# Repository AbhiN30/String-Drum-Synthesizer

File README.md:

# String/Drum Synthesizer (Initial Project Proposal)

## Team Members:
- Abhi Nayak (arnayak2) 
- Joel Schurgin (joelbs3)

## Problem
A musical artist brings with them a sense of how to evoke certain emotions or create particular atmospheres, but may lack the technical knowledge to bring it to life. Sound design can be challenging as it involves crafting the unique timbres and textures that define a piece of music, which can be both an art and a science. The learning curve is steep, not only because it requires a grasp of complex technical tools but also because it demands a creative intuition that isn't easily taught. Musicians and producers must learn to navigate a vast array of software and hardware tools, each with its own set of knobs, sliders, and buttons. Understanding how to shape sounds means diving deep into the physics of sound waves, the principles of digital signal processing, and the subtleties of different synthesis methods. This process can feel overwhelming, especially for beginners who might feel lost amidst the jargon and the sheer number of options.

## Solution
Our proposal is to build a synthesizer. A synthesizer is a machine that is capable of producing a range of sounds when given a simple key or noise pulse. The range of sounds are controlled by a set of parameters such as filter cutoffs, oscillator types, low frequency oscillators, etc. The proposed solution is two-fold. The first part of the project is to build emotive knobs that feature descriptive ranges such as soft to aggressive or thin to thick. These knobs would also control the internal parameters of the system to achieve the desired effects on the input sound. The other part is to create a system that records a sound and finds the best way to set the synthesizer's internal parameters to recreate it. The intended work flow of this device for a musical artist is to record a sound, tweak the knobs, and play that sound by pressing a key on a MIDI keyboard. It is up to the musician to record the sound into their own recording software for further manipulation.

# Solution Components
## Subsystem 1: Power Block

Purpose/Requirements: This subsystem must be able to power the processor and the USB keyboard. Capacitors will be used to stabilize the power block.

Components:

- 5V DC Power Supply Adapter
- Capacitors
- Subsystem 2: Synthesizer

## Subsystem 2: Software Synthesizer
Purpose/Requirements: This subsystem will generate sounds using the Karplus Strong algorithm which features a pulse generator and an echo chamber (modeled with digital delay, feedback, and filtering). When a note is played on a USB keyboard, this component must be able to change the pitch based on which key is pressed. The algorithm’s parameters must be controllable using potentiometers, but several parameters can be determined as a function of one knob. We chose the Karplus Strong algorithm to reduce the computational load, but we are modifying certain aspects to allow for a greater range of sounds. The pulse that we will use is a blend of noise and sine wave oscillator which are added together and distorted. In addition, there will be some soft distortion applied on the output. In addition, the echo chamber will use 3 IIR filters: highpass, lowpass, and a bell. The choice to use IIR filters is to lower the amount of computation.

We made a demo of the synthesizer algorithm using a digital audio workstation in order to play with parameters and determine the names of the emotive knobs. Below are the emotive knobs and how the corresponding synth parameters should change to implement them:

Aggression

- Synth Params: Pulse distortion, output distortion
- Knob Left: Low distortion
- Knob Right: High distortion

Brightness

- Synth Param: Low pass filter cutoff
- Knob Left: 20 Hz
- Knob Right: 20 kHz

Boominess

- Synth Param: High pass Cutoff
- Knob Left: 20 kHz
- Knob Center: Note pitch
- Knob Right: 20 Hz

Dampening

- Synth Param: Bell Q
- Knob Left: High Q
- Knob Right: Low Q

*Not sure what to call this yet, but it affects how the echo chamber resonates. Note: setting this to around 3.6 kHz sounds good, so it could be fine to keep this completely internal and forgo the corresponding knob.

- Synth Param: Bell frequency
- Knob Left: 20 hz
- Knob Right: 20 kHz

Scratchiness

- Synth Param: Length of pulse
- Knob Left: 0
- Knob Center: 1/(Note pitch)
- Knob Right: 4/(Note pitch)

Sharpness

- Synth Param: Mix between pulse noise and oscillator
- Knob Left: Pulse consists of only oscillator
- Knob Right: Pulse consists of only noise

*Strike weight => Corresponds to simulated weight of object striking the string/drum head.

- Synth Param: Pulse oscillator pitch
- Knob Left: 20 kHz
- Knob Right: 20 hz

Notes:
- The value "note pitch" is determined by USB keyboard input.
- Bell gain is fixed and should be set to attenuate the signal.

Components:

- Microprocessor
- DAC
- Potentiometers for parameters (linear, should be able to snap to center position if center value has meaning other should be smooth all the way through)
- USB Port

## Subsystem 3: Amplifier
Purpose/Requirements: This subsystem should output the smallest possible signal to noise ratio through a guitar cable or headphones. In order to achieve this we will experiment with using several inverting op-amp amplifier circuits in parallel and summing them together with an inverting mixer. The gain of each amplifier will be set, but the volume control will be part of the inverting mixer circuit.

Components:

- Mono 1/4in audio jack
- 4 Op-amps
- Logarithmic Potentiometer (for volume control)

## Subsystem 4: Screen/Monitor
Purpose/Requirements: This subsystem should display the waveform of the sound being processed. The purpose of this subsystem is for the user to be able to receive a visual representation of the sound they are developing using their input pulse and emotive knob manipulations. The screen could enhance the usability of the synthesizer by providing visual indicators or icons for each emotive knob, making it easier for users to identify how different settings affect the overall sound. This would bridge the gap between technical sound parameters and intuitive control.

Components:

- Mono 1/4in audio jack
- Op-amp/Transistors
- Raspberry Pi Screen, 7 inch portable monitor external display
# Criterion For Success
High-Level Goals:

1) Get a simple sound, such as a sine wave at 440 Hz, out of DAC output from the synthesizer subsystem. Should be viewable in an oscilloscope, but not important to hear yet.
2) Add potentiometers to the synthesizer and use to control pitch of simple sound for testing.
3) Build the amplifier in order to hear the previously described sound.
4) Add USB port and code for parsing keyboard input.
5) Use synthesizer algorithms to implement the emotive knobs, starting with the pulse generator and then building the echo chamber.
Reach Goal:

6) Implement the screen into the entire system. It will show the waveform of the generated sound, including its amplitude, frequency, and potential distortions. This helps users better grasp the effect of parameters like distortion, brightness, dampening, etc. This visualization would assist the user in creating more precise and desired sounds.

Important Notes:

-The screen is peripheral and not required for the rest of the system to operate. Therefore implementing it is a reach goal.

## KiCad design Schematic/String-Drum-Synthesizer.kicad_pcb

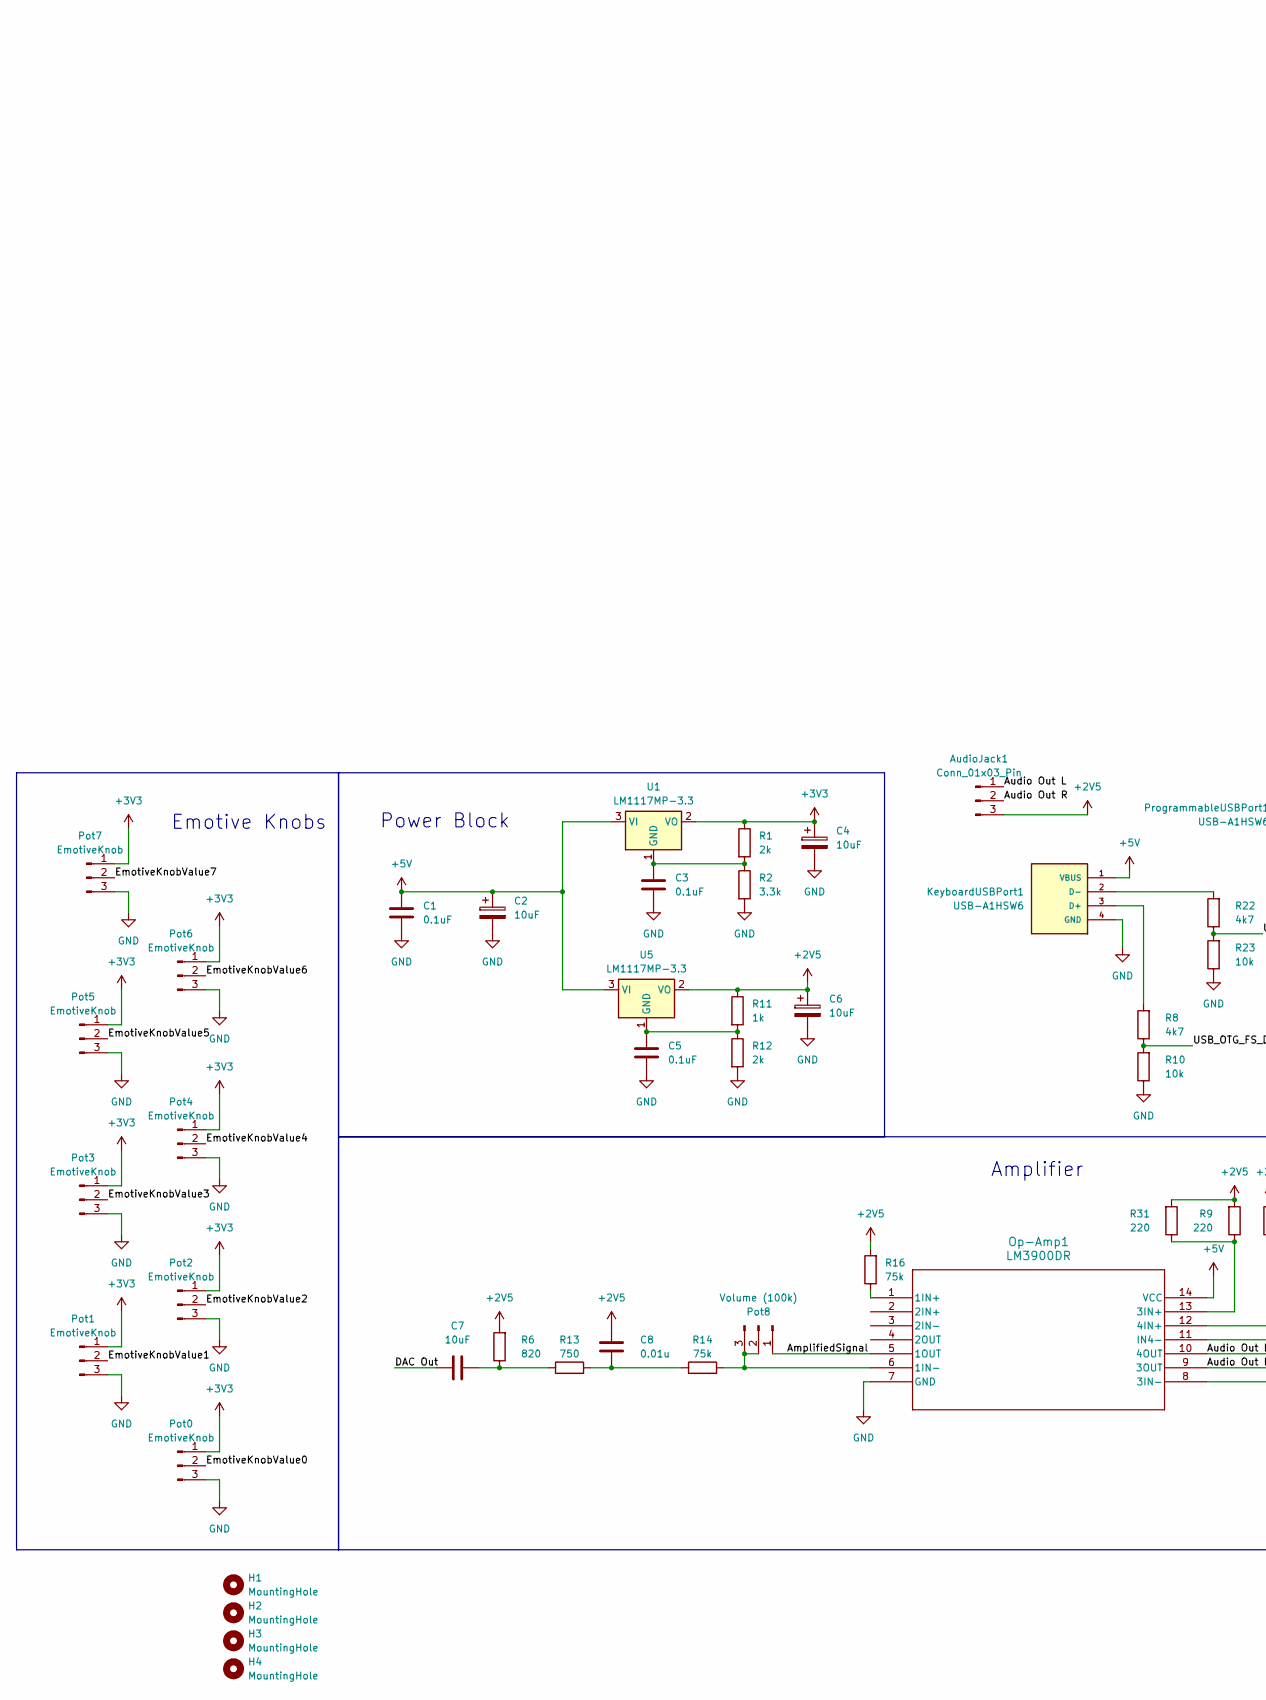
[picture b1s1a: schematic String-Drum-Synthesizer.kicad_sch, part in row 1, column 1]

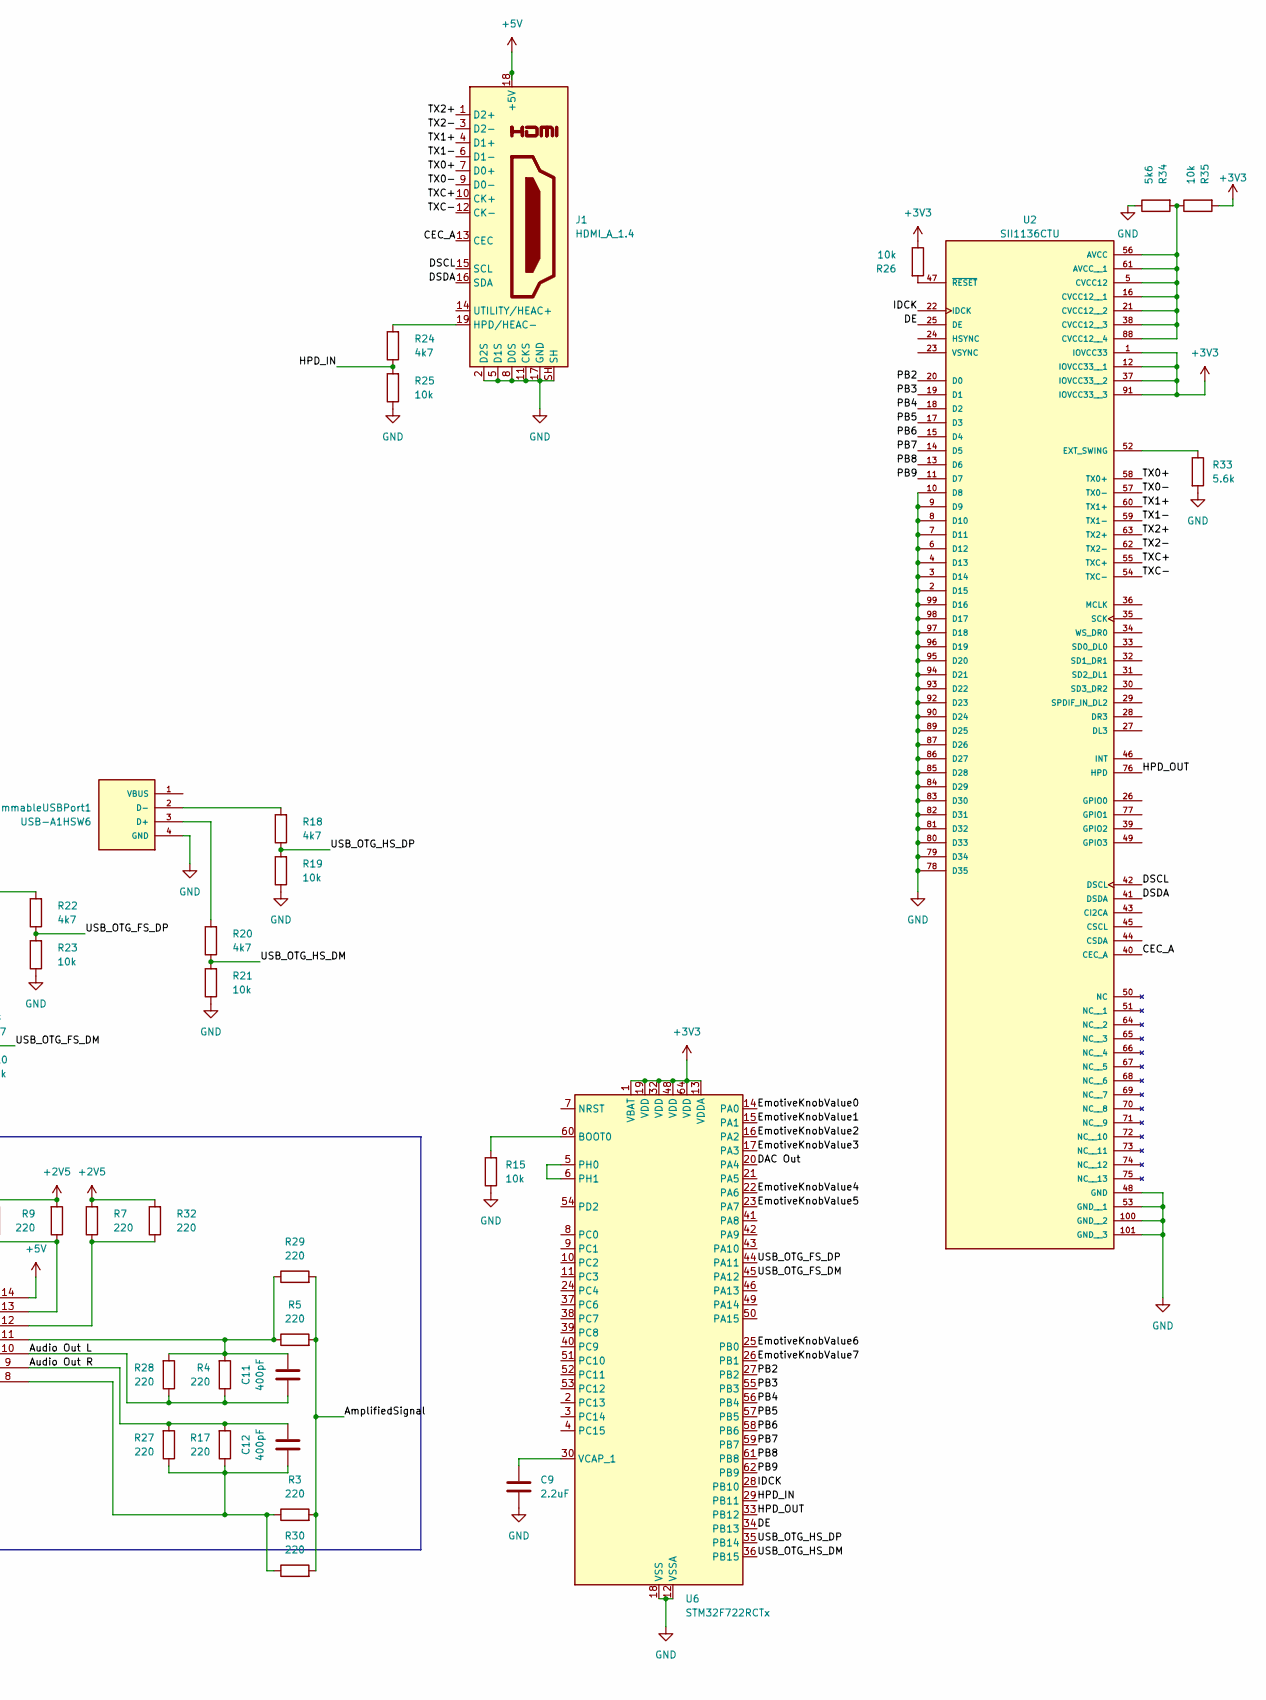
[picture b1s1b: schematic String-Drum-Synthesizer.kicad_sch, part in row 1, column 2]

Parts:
AudioJack1: Conn_01x03_Pin; Molex_KK-254_AE-6410-03A_1x03_P2.54mm_Vertical
C1, C3, C5: 0.1uF; C_Disc_D6.0mm_W4.4mm_P5.00mm
C2, C4, C6, C7: 10uF; CP_Radial_D7.5mm_P2.50mm
C8: 0.01u; C_Disc_D6.0mm_W4.4mm_P5.00mm
C9: 2.2uF; C_Disc_D6.0mm_W4.4mm_P5.00mm
C11, C12: 400pF; C_Disc_D6.0mm_W4.4mm_P5.00mm
H1, H2, H3, H4: MountingHole; MountingHole_3.2mm_M3
J1: HDMI_A_1.4; HDMI_A_Molex_208658-1001_Horizontal
KeyboardUSBPort1: USB-A1HSW6; OST_USB-A1HSW6; PARTREV A
Op-Amp1: LM3900DR; DIP-14_W7.62mm_Socket
Pot0, Pot1, Pot2, Pot3, Pot4, Pot5, Pot6, Pot7: EmotiveKnob; Molex_KK-254_AE-6410-03A_1x03_P2.54mm_Vertical
Pot8: Volume (100k); Molex_KK-254_AE-6410-03A_1x03_P2.54mm_Vertical
ProgrammableUSBPort1: USB-A1HSW6; OST_USB-A1HSW6; PARTREV A
R1, R12: 2k; R_Axial_DIN0207_L6.3mm_D2.5mm_P7.62mm_Horizontal
R2: 3.3k; R_Axial_DIN0207_L6.3mm_D2.5mm_P7.62mm_Horizontal
R3, R4, R5, R7, R9, R17, R27, R28, R29, R30, R31, R32: 220; R_Axial_DIN0207_L6.3mm_D2.5mm_P7.62mm_Horizontal
R6: 820; R_Axial_DIN0207_L6.3mm_D2.5mm_P7.62mm_Horizontal
R8, R18, R20, R22, R24: 4k7; R_Axial_DIN0207_L6.3mm_D2.5mm_P7.62mm_Horizontal
R10, R15, R19, R21, R23, R25, R26, R35: 10k; R_Axial_DIN0207_L6.3mm_D2.5mm_P7.62mm_Horizontal
R11: 1k; R_Axial_DIN0207_L6.3mm_D2.5mm_P7.62mm_Horizontal
R13: 750; R_Axial_DIN0207_L6.3mm_D2.5mm_P7.62mm_Horizontal
R14, R16: 75k; R_Axial_DIN0207_L6.3mm_D2.5mm_P7.62mm_Horizontal
R33: 5.6k; R_Axial_DIN0207_L6.3mm_D2.5mm_P7.62mm_Horizontal
R34: 5k6; R_Axial_DIN0207_L6.3mm_D2.5mm_P7.62mm_Horizontal
U1, U5: LM1117MP-3.3; SOT-223-3_TabPin2
U2: SII1136CTU; TQFP-100-1EP_14x14mm_P0.5mm_EP5x5mm
U6: STM32F722RCTx; LQFP-64_10x10mm_P0.5mm

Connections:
+2V5: AudioJack1.3, C6.1, C8.1, R6.2, R7.2, R9.2, R11.1, R16.2, R31.2, R32.2, U5.2 (VO)
+3V3: C4.1, Pot0.1, Pot1.1, Pot2.1, Pot3.1, Pot4.1, Pot5.1, Pot6.1, Pot7.1, R1.1, R26.1, R35.2, U1.2 (VO), U2.1 (IOVCC33), U2.12 (IOVCC33__1), U2.37 (IOVCC33__2), U2.91 (IOVCC33__3), U6.1 (VBAT), U6.13 (VDDA), U6.19 (VDD), U6.32 (VDD), U6.48 (VDD), U6.64 (VDD)
+5V: C1.1, C2.1, J1.18 (+5V), KeyboardUSBPort1.1 (VBUS), Op-Amp1.14 (VCC), U1.3 (VI), U5.3 (VI); also elsewhere on the board
/AmplifiedSignal: Op-Amp1.5 (1OUT), Pot8.1, R3.2, R5.2, R29.2, R30.2; also elsewhere on the board
/Audio Out L: AudioJack1.1, C11.1, Op-Amp1.10 (4OUT), R4.1, R28.1; also elsewhere on the board
/Audio Out R: AudioJack1.2, C12.2, Op-Amp1.9 (3OUT), R17.2, R27.2; also elsewhere on the board
/CEC_A: J1.13 (CEC), U2.40 (CEC_A)
/DAC Out: C7.1, U6.20 (PA4)
/DE: U2.25 (DE), U6.34 (PB13)
/DSCL: J1.15 (SCL), U2.42 (DSCL)
/DSDA: J1.16 (SDA), U2.41 (DSDA)
/EmotiveKnobValue0: Pot0.2, U6.14 (PA0)
/EmotiveKnobValue1: Pot1.2, U6.15 (PA1)
/EmotiveKnobValue2: Pot2.2, U6.16 (PA2)
/EmotiveKnobValue3: Pot3.2, U6.17 (PA3)
/EmotiveKnobValue4: Pot4.2, U6.22 (PA6)
/EmotiveKnobValue5: Pot5.2, U6.23 (PA7)
/EmotiveKnobValue6: Pot6.2, U6.25 (PB0)
/EmotiveKnobValue7: Pot7.2, U6.26 (PB1)
/HPD_IN: R24.1, R25.2, U6.29 (PB11)
/HPD_OUT: U2.76 (HPD), U6.33 (PB12)
/IDCK: U2.22 (IDCK), U6.28 (PB10)
/PB2: U2.20 (D0), U6.27 (PB2)
/PB3: U2.19 (D1), U6.55 (PB3)
/PB4: U2.18 (D2), U6.56 (PB4)
/PB5: U2.17 (D3), U6.57 (PB5)
/PB6: U2.15 (D4), U6.58 (PB6)
/PB7: U2.14 (D5), U6.59 (PB7)
/PB8: U2.13 (D6), U6.61 (PB8)
/PB9: U2.11 (D7), U6.62 (PB9)
/TX0+: J1.7 (D0+), U2.58 (TX0+)
/TX0-: J1.9 (D0-), U2.57 (TX0-)
/TX1+: J1.4 (D1+), U2.60 (TX1+)
/TX1-: J1.6 (D1-), U2.59 (TX1-)
/TX2+: J1.1 (D2+), U2.63 (TX2+)
/TX2-: J1.3 (D2-), U2.62 (TX2-)
/TXC+: J1.10 (CK+), U2.55 (TXC+)
/TXC-: J1.12 (CK-), U2.54 (TXC-)
/USB_OTG_FS_DM: R8.1, R10.2, U6.45 (PA12)
/USB_OTG_FS_DP: R22.1, R23.2, U6.44 (PA11)
/USB_OTG_HS_DM: R20.1, R21.2, U6.36 (PB15)
/USB_OTG_HS_DP: R18.1, R19.2, U6.35 (PB14)
GND: C1.2, C2.2, C3.2, C4.2, C5.2, C6.2, C9.2, J1.2 (D2S), J1.5 (D1S), J1.8 (D0S), J1.11 (CKS), J1.17 (GND), J1.SH, KeyboardUSBPort1.4 (GND), Op-Amp1.7 (GND), Pot0.3, Pot1.3, Pot2.3, Pot3.3, Pot4.3, Pot5.3, Pot6.3, Pot7.3, ProgrammableUSBPort1.4 (GND), R2.2, R10.1, R12.2, R15.1, R19.1, R21.1, R23.1, R25.1, R33.2, R34.1, U2.2 (D15), U2.3 (D14), U2.4 (D13), U2.6 (D12), U2.7 (D11), U2.8 (D10), U2.9 (D9), U2.10 (D8), U2.48 (GND), U2.53 (GND__1), U2.78 (D35), U2.79 (D34), U2.80 (D33), U2.81 (D32), U2.82 (D31), U2.83 (D30), U2.84 (D29), U2.85 (D28), U2.86 (D27), U2.87 (D26), U2.89 (D25), U2.90 (D24), U2.92 (D23), U2.93 (D22), U2.94 (D21), U2.95 (D20), U2.96 (D19), U2.97 (D18), U2.98 (D17), U2.99 (D16), U2.100 (GND__2), U2.101 (GND__3), U6.12 (VSSA), U6.18 (VSS), U6.31 (VSS), U6.47 (VSS), U6.63 (VSS); also elsewhere on the board
unnamed: C7.2, R6.1, R13.1
unnamed: C8.2, R13.2, R14.1
unnamed: J1.19 (HPD/HEAC-), R24.2
unnamed: KeyboardUSBPort1.3 (D+), R8.2
unnamed: KeyboardUSBPort1.2 (D-), R22.2
unnamed: Op-Amp1.1 (1IN+), R16.1
unnamed: Op-Amp1.6 (1IN-), Pot8.2, Pot8.3, R14.2
unnamed: Op-Amp1.13 (3IN+), R9.1, R31.1
unnamed: C12.1, Op-Amp1.8 (3IN-), R3.1, R17.1, R27.1, R30.1
unnamed: Op-Amp1.12 (4IN+), R7.1, R32.1
unnamed: C11.2, Op-Amp1.11 (IN4-), R4.2, R5.1, R28.2, R29.1
unnamed: ProgrammableUSBPort1.3 (D+), R20.2
unnamed: ProgrammableUSBPort1.2 (D-), R18.2
unnamed: C3.1, R1.2, R2.1, U1.1 (GND)
unnamed: R34.2, R35.1, U2.5 (CVCC12), U2.16 (CVCC12__1), U2.21 (CVCC12__2), U2.38 (CVCC12__3), U2.56 (AVCC), U2.61 (AVCC__1), U2.88 (CVCC12__4)
unnamed: R33.1, U2.52 (EXT_SWING)
unnamed: R26.2, U2.47 (~RESET)
unnamed: C5.1, R11.2, R12.1, U5.1 (GND)
unnamed: R15.2, U6.60 (BOOT0)
unnamed: U6.5 (PH0), U6.6 (PH1)
unnamed: C9.1, U6.30 (VCAP_1)

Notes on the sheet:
Amplifier
Power Block
Emotive Knobs

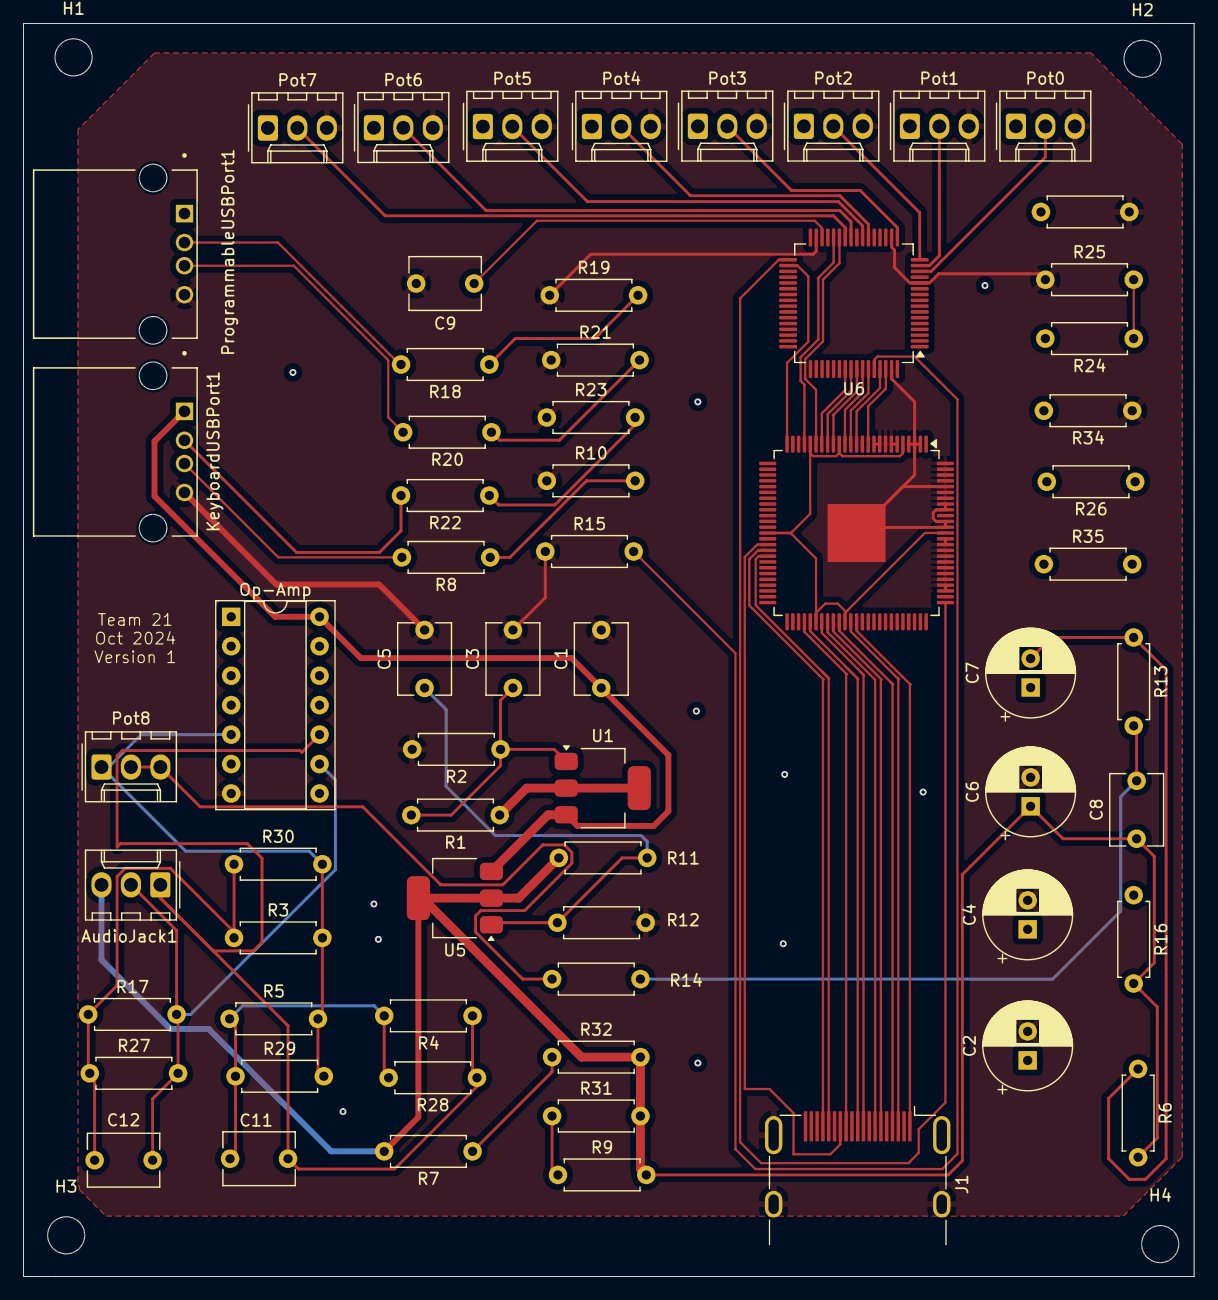
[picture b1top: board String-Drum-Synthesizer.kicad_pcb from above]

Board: 2 copper layers, 101.0 x 108.1 mm, 68 parts (0 on the bottom side), 63 nets.

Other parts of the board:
Op-Amp: LM3900DR; DIP-14_W7.62mm_Socket

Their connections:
+5V: Op-Amp.14 (VCC); also elsewhere on the board
/AmplifiedSignal: Op-Amp.5 (1OUT); also elsewhere on the board
/Audio Out L: Op-Amp.10 (4OUT); also elsewhere on the board
/Audio Out R: Op-Amp.9 (3OUT); also elsewhere on the board
GND: Op-Amp.7 (GND); also elsewhere on the board

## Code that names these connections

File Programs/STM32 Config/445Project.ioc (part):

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Mcu.Name=STM32F722R(C-E)Tx
Mcu.Package=LQFP64
Mcu.UserName=STM32F722RCTx
PA0-WKUP.Signal=ADCx_IN0
PA1.Signal=ADCx_IN1
PA11.Mode=Device_Only
PA11.Signal=USB_OTG_FS_DM
PA12.Mode=Device_Only
PA12.Signal=USB_OTG_FS_DP
PA13.Mode=Serial_Wire
PA13.Signal=SYS_JTMS-SWDIO
PA14.Mode=Serial_Wire
PA14.Signal=SYS_JTCK-SWCLK
PA2.Signal=ADCx_IN2
PA3.Signal=ADCx_IN3
PA4.Signal=COMP_DAC1_group
PA5.Signal=ADCx_IN5
PA6.Signal=ADCx_IN6
PA7.Signal=ADCx_IN7
PA9.Mode=Activate_VBUS
PA9.Signal=USB_OTG_FS_VBUS
PB0.Signal=ADCx_IN8
PB1.Signal=ADCx_IN9
PB10.Signal=GPIO_Output
PB11.Signal=GPIO_Output
PB12.Signal=GPIO_Output
PB13.Signal=GPIO_Output
PB14.Mode=Internal_Phy_Device
PB14.Signal=USB_OTG_HS_DM
PB15.Mode=Internal_Phy_Device
PB15.Signal=USB_OTG_HS_DP
PB2.Signal=GPIO_Output
PB3.Signal=GPIO_Output
PB4.Signal=GPIO_Output
PB5.Signal=GPIO_Output
PB6.Signal=GPIO_Output
PB7.Signal=GPIO_Output
PB8.Signal=GPIO_Output
PB9.Signal=GPIO_Output
PH0-OSC_IN.Mode=HSE-External-Oscillator
PH0-OSC_IN.Signal=RCC_OSC_IN
PH1-OSC_OUT.Mode=HSE-External-Oscillator
PH1-OSC_OUT.Signal=RCC_OSC_OUT
RCC.HSE_VALUE=25000000
RCC.SYSCLKFreq_VALUE=48000000
RCC.SYSCLKSource=RCC_SYSCLKSOURCE_PLLCLK
board=custom

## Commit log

2024-09-17 Added notebooks
2024-09-17 Updating README.md with Project Proposal Details
2024-09-25 Schematic created
2024-09-25 Power block done
2024-09-26 Emotive Knobs in progress
2024-10-02 Emotive Knob subsytem added
2024-10-02 Amplifier subsystem added
2024-10-02 Still needs proc details
2024-10-04 Most recent schematic
2024-10-04 Updated Amplifier Resistor Values
2024-10-08 Final Schematic For Demo
2024-10-08 Deleted a USB Port
2024-10-14 Port added to schematic, but needs connections
2024-10-14 Switched out op-amp for actual LM3900
2024-10-14 Adding peripheral USB hardware
2024-10-14 Added HDMI Chip
2024-10-14 Added HDMIconfiguration
2024-10-14 Current USB Port
2024-10-14 Added gitignore
2024-10-17 Schematic Done!!
2024-10-17 Needs R and C Footprints
2024-10-18 Fixed multiplexor pinout
2024-10-22 Fixed HDMI Pinout. Have to start PCB design over
2024-10-22 Deleted old traces
2024-10-23 Current Schem
2024-10-23 Current changes
2024-10-23 SCHEMATIC COMPLETE
2024-10-23 Half the copper traces work
2024-10-28 Hopefully this layout is good
2024-10-28 Is it done?
2024-10-28 Yes it is done
2024-11-13 C Program with USB Flashing + Emotive Controls (Untested)
2024-11-14 Updated code to accommodate single ADC configuration
2024-11-14 Added in Sine Wave Test Code
2024-11-14 Incorporated Audio PLL
2024-11-17 Implemented Sine Wave Test + Added Pin Config File
2024-11-17 Working on adding audio buffer
2024-11-20 One Emotive Knob Works
2024-11-20 Code written for I2S, but still testing
2024-11-21 Double buffer works!
2024-11-27 Attempt at MIDI communication using USB_OTG_FS
2024-11-28 Can read midi messages!!!
2024-12-02 Can output sawtooth, but none of Karplus-Strong is implemented
2024-12-02 Created EmotiveKnob Class
2024-12-02 First Attempt Visualizing Waveform
2024-12-02 Fixed Errors for Attempt 1
2024-12-02 Fixed more errors
2024-12-02 Bug Fixes
2024-12-04 EMOTIVE KNOBS WORK
2024-12-08 Final Code
2024-12-12 Added Image to Notebook
2024-12-12 Rename Physical Design Drawing.png to Physical-Design.png
2024-12-16 Added Images Folder
2024-12-16 Adding Images Folder
2024-12-16 Added schematic
2024-12-16 Added image
2024-12-16 Added images
2024-12-16 Trouble commiting my images (Joel)
2024-12-17 Accidentally deleted Abhi's README.md (Joel)
2024-12-17 Added more images
2024-12-17 This should be in .gitignore
